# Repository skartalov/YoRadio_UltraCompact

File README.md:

This is custom project for YoRadio using 240x240 display, UDA1334 I2S stereo DAC, Li-Po battery charger, 3 way slide button.

Open the schematic and the board with EaglePCB.

Included are: myoptions.h for this specific board and some nice internet radios in playlist.csv

Use this on your own risk, no any support is included. Please don't ask questions. If you know what you are doing you will be able to build this project by your own. If you have questions - this project is not for you.

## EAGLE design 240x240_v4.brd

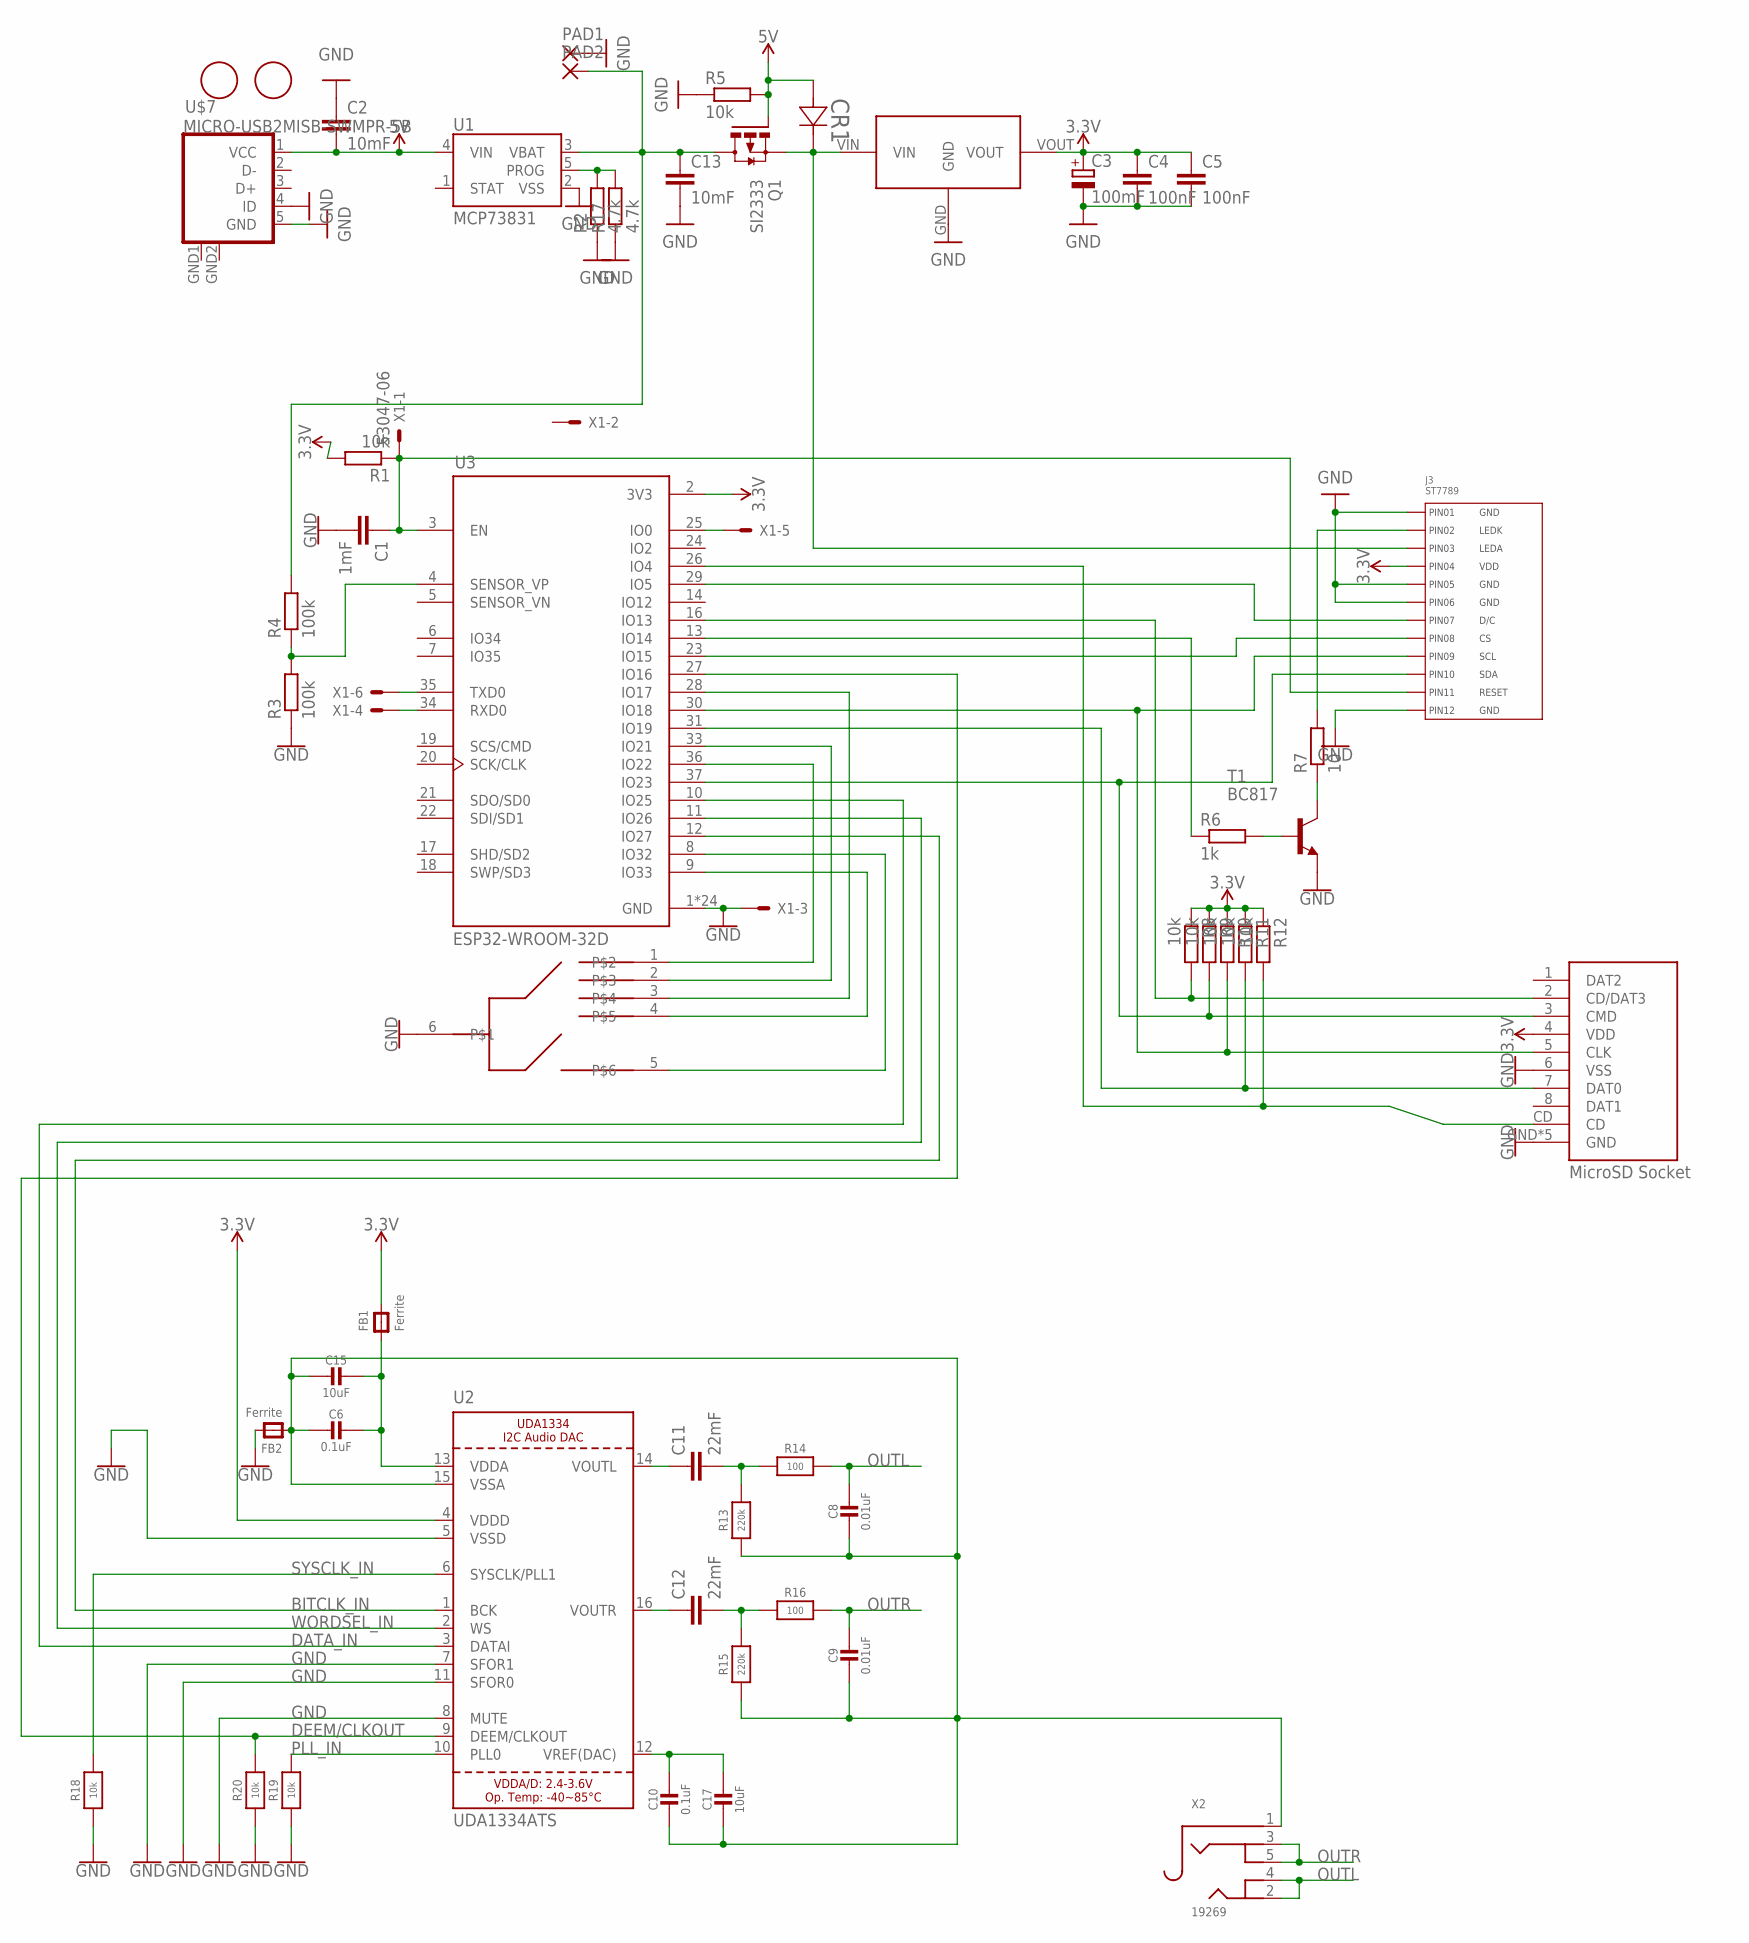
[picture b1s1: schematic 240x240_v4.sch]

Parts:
C1: 1mF; C0603
C2, C13: 10mF; C0603
C3: 100mF; SMC_B
C4, C5: 100nF; C0805K
C6, C10: 0.1uF; 0805-NO
C8, C9: 0.01uF; 0805-NO
C11, C12: 22mF; C1210
C15, C17: 10uF; 0805-NO
CR1: BAT48; SOD-123_STM-M
FB1, FB2: Ferrite; 0805
J3: ST7789; ST7789_CONNECTOR
PAD1, PAD2: SMD2; SMD1,27-2,54
Q1: SI2333; SUPER-SOT3
R1, R5, R8, R9, R10, R11, R12: 10k; R0603
R2, R17: 4.7k; R0805
R3, R4: 100k; R0603
R6: 1k; R0603
R7: 10; R0805
R13, R15: 220k; 0805-NO
R14, R16: 100; 0805-NO
R18, R19, R20: 10k; 0603-NO
T1: BC817; SOT23-BEC
U1: MCP73831; SOT23-5
U2: UDA1334ATS; SSOP16_4.4MM
U3: ESP32-WROOM-32D; MODULE_ESP32-WROOM-32D
U$1: XC6203; SOT89
U$2: B5-P5S-0D; B5-P5S-0D-Z
U$3, U$4: FIDUCIAL; FIDUCIAL_1MM
U$5: ATTEND_MICROSD_SOCKET
U$7: MICRO-USB2MISB-SWMPR-5B; MICRO-USB2
X1: 53047-06
X2: 19269; 4UCONN_19269

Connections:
3.3V: C3.+, C4.1, C5.1, FB1.2, J3.P$4 (4), R1.2, R8.1, R9.1, R10.1, R11.1, R12.1, U2.4 (VDDD), U3.2 (3V3), U$1.VOUT, U$5.4 (VDD)
5V: C2.2, CR1.1, Q1.1 (G), R5.2, U1.4 (VIN), U$7.1 (VCC)
BITCLK_IN: U2.1 (BCK), U3.12 (IO27)
DATA_IN: U2.3 (DATAI), U3.10 (IO25)
DEEM/CLKOUT: R20.2, U2.9 (DEEM/CLKOUT), U3.27 (IO16)
GND: C1.2, C2.1, C3.-, C4.2, C5.2, C13.2, FB2.2, J3.P$1 (1), J3.P$5 (5), J3.P$6 (6), J3.P$12 (12), PAD1.1, R2.1, R3.1, R5.1, R17.1, R18.1, R19.1, R20.1, T1.E, U1.2 (VSS), U2.5 (VSSD), U2.7 (SFOR1), U2.8 (MUTE), U2.11 (SFOR0), U3.1 (GND), U3.15 (GND), U3.38 (GND), U3.39_1 (GND), U3.39_2 (GND), U3.39_3 (GND), U3.39_4 (GND), U3.39_5 (GND), U3.39_6 (GND), U3.39_7 (GND), U3.39_8 (GND), U3.39_9 (GND), U3.39_10 (GND), U3.39_11 (GND), U3.39_12 (GND), U3.39_13 (GND), U3.39_14 (GND), U3.39_15 (GND), U3.39_16 (GND), U3.39_17 (GND), U3.39_18 (GND), U3.39_19 (GND), U3.39_20 (GND), U3.39_21 (GND), U$1.GND, U$2.6, U$5.6 (VSS), U$5.GND, U$5.GND2 (GND), U$5.GND3 (GND), U$5.GND4 (GND), U$5.GND5 (GND), U$7.4 (ID), U$7.5 (GND), U$7.GND1 (GND), U$7.GND2 (GND), X1.3
unnamed: C1.1, J3.P$11 (11), R1.1, U3.3 (EN), X1.1
unnamed: J3.P$9 (9), R10.2, U3.30 (IO18), U$5.5 (CLK)
unnamed: J3.P$10 (10), R9.2, U3.37 (IO23), U$5.3 (CMD)
unnamed: J3.P$7 (7), U3.29 (IO5)
unnamed: J3.P$8 (8), U3.23 (IO15)
unnamed: U3.35 (TXD0), X1.6
unnamed: U3.34 (RXD0), X1.4
unnamed: R3.2, R4.1, U3.4 (SENSOR_VP)
unnamed: R6.2, T1.B
unnamed: U3.36 (IO22), U$2.1
unnamed: R2.2, R17.2, U1.5 (PROG)
unnamed: J3.P$2 (2), R7.2
unnamed: U3.33 (IO21), U$2.2
unnamed: U3.28 (IO17), U$2.3
unnamed: U3.9 (IO33), U$2.4
unnamed: U3.8 (IO32), U$2.5
unnamed: R11.2, U3.31 (IO19), U$5.7 (DAT0)
unnamed: C13.1, PAD2.1, Q1.3 (D), R4.2, U1.3 (VBAT)
unnamed: U3.25 (IO0), X1.5
unnamed: R7.1, T1.C
unnamed: R6.1, U3.13 (IO14)
unnamed: R8.2, U3.16 (IO13), U$5.2 (CD/DAT3)
unnamed: R12.2, U3.26 (IO4), U$5.CD
unnamed: C6.1, C15.1, FB1.1, U2.13 (VDDA)
unnamed: C11.2, R13.2, R14.1
unnamed: C12.2, R15.2, R16.1
unnamed: C10.1, C17.1, U2.12 (VREF(DAC))
unnamed: C12.1, U2.16 (VOUTR)
unnamed: C11.1, U2.14 (VOUTL)
unnamed: CR1.2, J3.P$3 (3), Q1.2 (S), U$1.VIN
unnamed: C6.2, C8.2, C9.2, C10.2, C15.2, C17.2, FB2.1, R13.1, R15.1, U2.15 (VSSA), X2.1
OUTL: C8.1, R14.2, X2.2, X2.4
OUTR: C9.1, R16.2, X2.3, X2.5
PLL_IN: R19.2, U2.10 (PLL0)
SYSCLK_IN: R18.2, U2.6 (SYSCLK/PLL1)
WORDSEL_IN: U2.2 (WS), U3.11 (IO26)

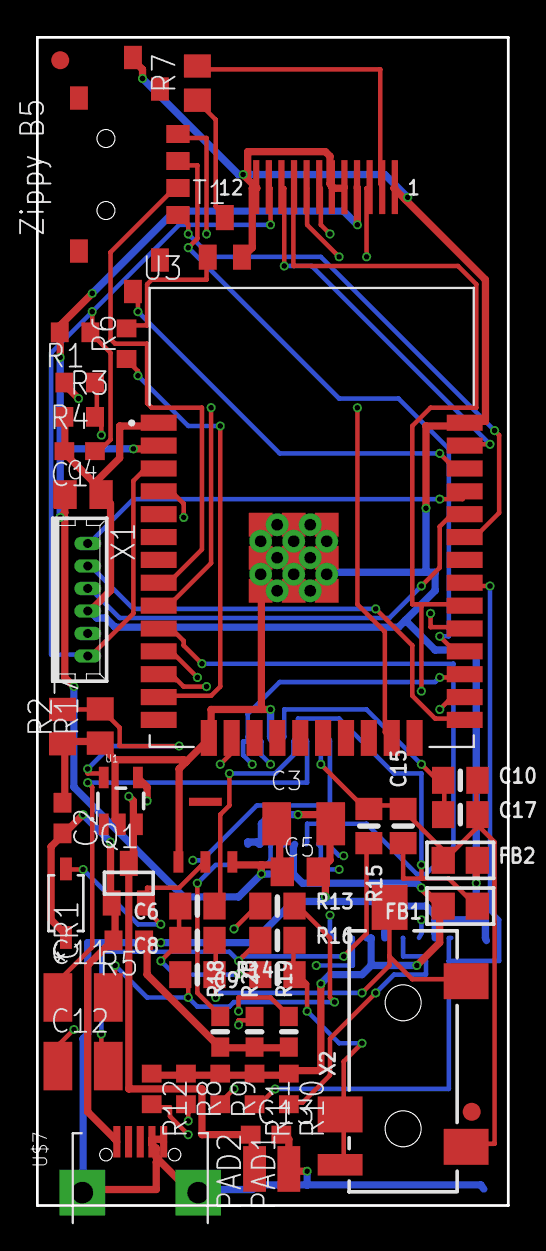
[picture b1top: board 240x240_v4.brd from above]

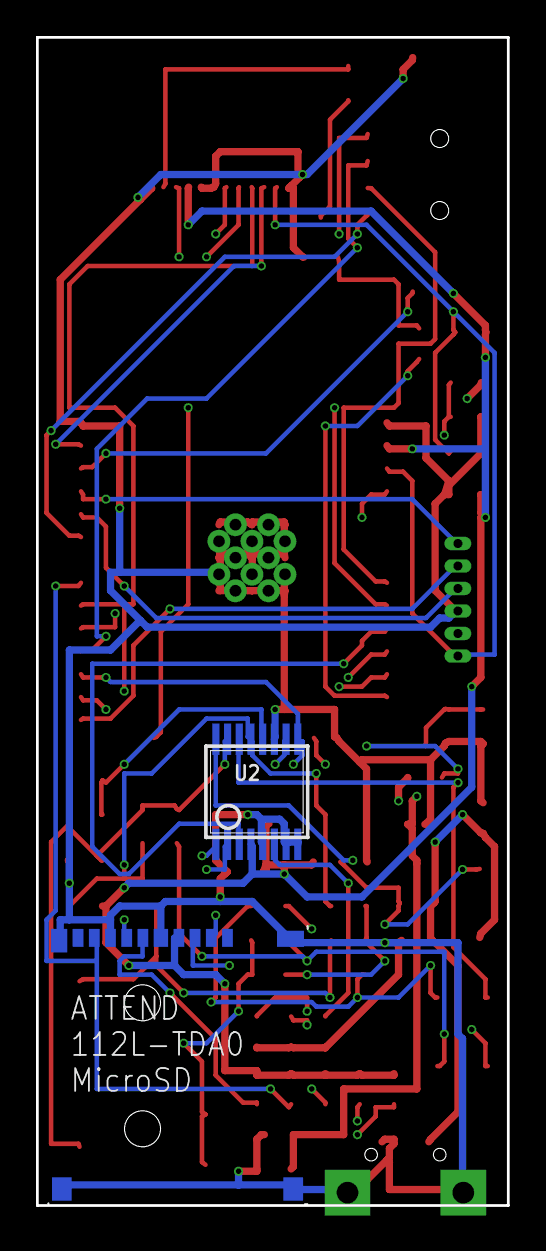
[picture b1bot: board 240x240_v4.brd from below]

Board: 4 copper layers, 26.2 x 64.9 mm, 53 parts (2 on the bottom side), 42 nets.

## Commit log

2026-04-16 Add usage disclaimer to README
    Added a disclaimer about project usage and support.

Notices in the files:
parts and their libraries:
SparkFun-IC-Power: Licensing: Creative Commons ShareAlike 4.0 International - https://creativecommons.org/licenses/by-sa/4.0
microbuilder: This work is placed in the public domain, and may be freely used for commercial and non-commercial work with the following conditions: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
